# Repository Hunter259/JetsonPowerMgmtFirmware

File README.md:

# JetsonPowerMgmtFirmware
IPMI firmware for STM32 devices to control the Jetson Power Mangement Module

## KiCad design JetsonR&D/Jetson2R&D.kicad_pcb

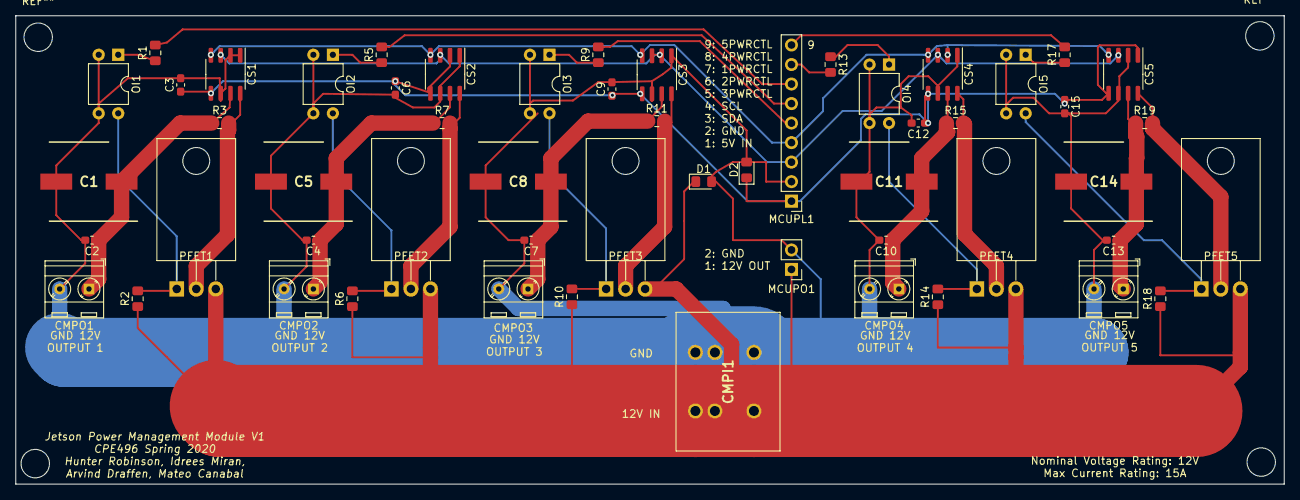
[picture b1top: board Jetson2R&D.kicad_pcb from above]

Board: 2 copper layers, 165.1 x 61.0 mm, 55 parts (0 on the bottom side), 30 nets.

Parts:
C1, C5, C8, C11, C14: 1000uF; CAPAE1030X1050N
C2, C3, C4, C6, C7, C9, C10, C12, C13, C15: 0.1uF; C_0603_1608Metric_Pad1.05x0.95mm_HandSolder
CMPI1: Screw_Terminal_01x02; 1720576
CMPO1, CMPO2, CMPO3, CMPO4, CMPO5: Screw_Terminal_01x02; TerminalBlock_MetzConnect_Type086_RT03402HBLC_1x02_P3.81mm_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
CS1, CS2, CS3, CS4, CS5: INA219AxD; SOIC-8_3.9x4.9mm_P1.27mm
D1, D2: D_Schottky; D_0805_2012Metric_Pad1.15x1.40mm_HandSolder
MCUPL1: Conn_01x09_Male; PinHeader_1x09_P2.54mm_Vertical
MCUPO1: Conn_01x02_Female; PinHeader_1x02_P2.54mm_Vertical
OI1, OI2, OI3, OI4, OI5: LTV-817; DIP-4_W7.62mm
PFET1, PFET2, PFET3, PFET4, PFET5: SUP70101EL-GE3; TO-220-3_Horizontal_TabDown
R1, R5, R9, R13, R17: 1200; R_0805_2012Metric_Pad1.15x1.40mm_HandSolder
R2, R6, R10, R14, R18: 6.8k; R_0805_2012Metric_Pad1.15x1.40mm_HandSolder
R3, R7, R11, R15, R19: 0.005; R_0805_2012Metric_Pad1.15x1.40mm_HandSolder

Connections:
/MasterPWRCTL: MCUPL1.7, R1.2
GND: C1.2, C2.2, C3.2, C4.2, C5.2, C6.2, C7.2, C8.2, C9.2, C10.2, C11.2, C12.2, C13.2, C14.2, C15.2, CMPI1.4, CMPI1.5, CMPI1.6, CMPO1.2, CMPO2.2, CMPO3.2, CMPO4.2, CMPO5.2, CS1.1, CS1.2, CS1.6, CS2.1, CS2.6, CS3.1, CS3.6, CS4.1, CS4.6, CS5.2, CS5.6, D1.2, D2.2, MCUPL1.2, MCUPO1.2, OI1.2, OI1.3, OI2.2, OI2.3, OI3.2, OI3.3, OI4.2, OI4.3, OI5.2, OI5.3
unnamed: C1.1, C2.1, CMPO1.1, CS1.7, R3.1
unnamed: C4.1, C5.1, CMPO2.1, CS2.7, R7.1
unnamed: C7.1, C8.1, CMPO3.1, CS3.7, R11.1
unnamed: C10.1, C11.1, CMPO4.1, CS4.7, R15.1
unnamed: C13.1, C14.1, CMPO5.1, CS5.7, R19.1
unnamed: CS1.8, PFET1.2, R3.2
unnamed: CS2.8, PFET2.2, R7.2
unnamed: CS3.8, PFET3.2, R11.2
unnamed: CS4.8, PFET4.2, R15.2
unnamed: CS5.8, PFET5.2, R19.2
unnamed: OI1.1, R1.1
unnamed: OI1.4, PFET1.1, R2.2
unnamed: OI2.1, R5.1
unnamed: OI2.4, PFET2.1, R6.2
unnamed: OI3.1, R9.1
unnamed: OI3.4, PFET3.1, R10.2
unnamed: OI4.1, R13.1
unnamed: OI4.4, PFET4.1, R14.2
unnamed: OI5.1, R17.1
unnamed: OI5.4, PFET5.1, R18.2
SCL: CS1.4, CS2.4, CS3.4, CS4.2, CS4.4, CS5.4, MCUPL1.4
SDA: CS1.3, CS2.3, CS3.2, CS3.3, CS4.3, CS5.3, MCUPL1.3
Slave1PWRCTL: MCUPL1.6, R5.2
Slave2PWRCTL: MCUPL1.5, R9.2
Slave3PWRCTL: MCUPL1.8, R13.2
Slave4PWRCTL: MCUPL1.9, R17.2
VCC: C3.1, C6.1, C9.1, C12.1, C15.1, CS1.5, CS2.2, CS2.5, CS3.5, CS4.5, CS5.1, CS5.5, D2.1, MCUPL1.1
VDD: CMPI1.1, CMPI1.2, CMPI1.3, D1.1, MCUPO1.1, PFET1.3, PFET2.3, PFET3.3, PFET4.3, PFET5.3, R2.1, R6.1, R10.1, R14.1, R18.1

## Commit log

2020-03-15 Initial Commit
    Created NanoFramework VS Project
    Created GPIO PWR Control Class
    Created INA219 Control Class
2020-04-16 Finished initial configuration of INA219 Added reading bus voltage and currents from single INA219's and from all INA219's Added register enumeration for better readability
2020-04-16 Fixed code style issues. Removed unused variable INACount. Changed readonly variables to proper const type.
2020-04-16 Added GPIOPinDefs structure for ease of use. Finished constructor with power set to off at default. Added independent power control functions. Added entire cluster power control functions.
2020-04-17 Fixed styling issues. Commented all required sections.
2020-04-17 Finished commenting functions and configuration register code Finished fixing styling errors.
2020-04-17 Initial commit for JSON serialization of user defined configurations Fully commented and style checked
2020-04-17 Added structure to hold all values for INA219 returns Added functions to return the previously mentioned structure as a signle specified INA219 or all of them.
2020-04-17 Fixed an inconsistency with some comments
2020-04-17 Fixed a namespace matching class type issue
2020-04-17 Initial commit to main. Contains initial setup.
2020-04-27 Added the Jetson PMS schematics and routing for ease of access.
